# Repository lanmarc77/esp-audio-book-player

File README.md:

# TINAMP: An ESP32 based audio book player build from existing electronics modules
TINAMP: **T**his **I**s **N**ot **A** **M**usic **P**layer.  
  
This is a device that is meant to play non-DRM audio books from SD cards and has the following features:  

- folder based audio book player, one folder contains all files of one audio book
- multiple audio books supported (currently max. 9999 on one SD card with presorted index)
- sorting of audio book names and audio book files by ASCII name (see limitations of sorting below)
- saves audio book listening position and resumes for each audio book
- supports huge single file audio books, e.g. a 20hrs long singe file audio book
- file formats AMR-WB, MP3 and OGG
- ASCII character based menu driven UI for 16x4 character screen
- single rotary encoder navigation
- sleep timer 1...480min, wakeup timer 1min...24hr
- play speed settings from 0.5...2.5 in 0.05 steps (saved individually for each audio book)
- audio equalizer (saved individually for each audio book)
- endless auto repeat mode of selected audio book
- auto power off
- firmware upgrades from SD card
- based on pure esp-idf + esp-adf
- plays 50hrs+ with 2800mAh 18650 battery
- does not need nor use any wireless connection
- does not track the user in any way
- charging via USB-C
- endless options of integrations with speakers/cases
  
It tries to follow the design principle of
[doing one thing and doing that well](https://en.wikipedia.org/wiki/Unix_philosophy).
  
# The working prototypes
development board:

integrated in an old speaker that otherwise might have landed in the trash:  

the current portable/smaller prototype version (based on Hammond RL6215 case):  

first 3d print prototype with 80s vibes:  

[first POC (proof of concept)](pictures/first_poc.jpg)
  
# Why?
By the time of this writing (2023) one really needs to search hard to find an offline only non tracking audio book player that is
able to play files from huge SD cards and at the same time sorts the files based on their name and remembers and
resumes the last listening position.  
Many people nowadays will use subscription services with corresponding apps on their smartphone. These services
and the apps usually track the users build profiles suggest new audio books sell ads and more. Services like these can be canceled at any time. May it be for politics or economic reasons. They usually do not allow you to own the audio book but only sell a license to listen at it for as long as the company exists or is allowed to do business with you.  
I have an audio book collection that I created by only buying if I can download the files or copy them e.g. from a CD to keep them. Without any DRM.  
All my audio books are converted to and then stored in AMR-WB as for me the quality with 24kBit/s mono is good enough.
This shrinks an MP3 file to approx. 1/10ths when using AMR-WB and also makes the backup cheap. One CD with AMR-WB can hold 60hrs, a DVD 350hrs, a 25GB BD-R 2000hrs+.  
A 256GB SD card can hold around 2 years and 9 months of continuous listening in AMR-WB. Multiple SD cards can hold enough listening material for a life time.  
Using existing electronics hardware modules and the software of this repository I can now build a device that just plays my audio books. Not more, not less. And it most likely will do so in 30years assuming nothing breaks.
There are still 30yrs+ old Nintendo Gameboys that work like a charm and are being refurbished.  
Additionally I can change the behavior of the software as I like. The whole development environment works offline and can also be installed in an offline virtual machine and will still be able to compile even if the hardware manufacturer of the main controller board does not exist anymore.  
  
# Videos
Download and watch:  
[Scenario1](https://github.com/lanmarc77/esp-audio-book-player/raw/main/videos/scenario1.mp4): normal operation  
[Scenario2](https://github.com/lanmarc77/esp-audio-book-player/raw/main/videos/scenario2.mp4): seeking  
[Scenario3](https://github.com/lanmarc77/esp-audio-book-player/raw/main/videos/scenario3.mp4): sorting  
[Scenario4](https://github.com/lanmarc77/esp-audio-book-player/raw/main/videos/scenario4.mp4): auto bookmarks  
[Scenario5](https://github.com/lanmarc77/esp-audio-book-player/raw/main/videos/scenario5.mp4): sleep timer  
[Scenario6](https://github.com/lanmarc77/esp-audio-book-player/raw/main/videos/scenario6.mp4): wakeup timer  
[Scenario7](https://github.com/lanmarc77/esp-audio-book-player/raw/main/videos/scenario7.mp4): firmware upgrade  
[Scenario8](https://github.com/lanmarc77/esp-audio-book-player/raw/main/videos/scenario8.mp4): play speed, equalizer, repeat mode  
  
# Hardware
The build only needs a few components that are manufactured by companies in mass and therefore cheap.  
For PCB based components the schematics are available in the module datasheets folder.  
  
**Main controller board:**  
The main controller board is a Heltec WiFi Kit 32 V3. It was chosen because it has a very small deep sleep
current of about 10µA. I measured 15µA with nothing connected to it. Still very good. It already comes with
the circuitry to connect and charge a rechargeable battery as well as the possibility to disconnect other
components from power by using a software programmable power pin (Ve).  
Finally an OLED display is also already available for the UI.  
Be aware that you buy V3 of this board version as it has the low deep sleep current. Otherwise your battery
looses way too much energy even if you do not use the player. Additionally verify that you also get a fitting
battery cable.  
  
Typical price in Germany incl. tax (2023): 20€. 
  
**I²S digital analog audio converter**  
Currently only a MAX98357A based converter has been tested extensively. Also an UDA1334A and PCM5102 were
tested and they worked. Both of these stereo DACs needed around 10-15mA more current which will reduce the system
runtime.
The MAX98357A already contains an amplifier to directly connect it to a speaker and get a usable volume out
of it.  
  
Typical price in Germany incl. tax (2023): 8€. 
  
**SD card holder**  
I still had old big SD cards laying around so I started with a big SD card holder. They also exists in
micro sd card format. I used this model as it comes with the needed pullup resistors already on the PCB.
Additionally I removed the voltage regulator that is used to convert 5V to 3.3V as I drive the board already
with 3.3V and it consumed around 2mA if back fed. I tested SD cards up to 512GB with this board and they worked.  
  
Typical price in Germany incl. tax (2023): 1.5€. 
  
**Battery and holder**  
Any LiIon battery can be used. I tried 18650 and 14500 without any problems. I suggest trusted dealers as
there are many cheap fake batteries.  
  
Typical price in Germany for both incl. tax (2023): 8€. 
  
**Rotary encoder**  
To minimize wiring and drilling work I decided for a single rotary encoder as main navigation option. This model
has an integrated switch. I suggest to buy a version that comes with the washer/nut/cap.  
  
Typical price in Germany incl. tax (2023): 1€. 
  
**PCB**  
The prototypes as seen above use half or full size euro card PCBs. Any will do for manual wiring. You would
use the full size if you need the extra space for mounting it inside e.g. a speaker.  
  
Typical price in Germany incl. tax (2023): 2€. 
  
## Wiring diagram
Click on the picture for zoom.  

The original .odt file of this drawing is in the `src`directory.  
  
Pictures of manually wired PCB:  

These PCBs have headers for the components. You can leave these out but then need to make sure in 
which order you solder the wires as you might not get to them anymore.   
  
## Buyable manufactured PCB
WIP: One or two PCB layouts as motherboard for a 3D printed base case and a worldwide buyable case.  
First prototype PCB:  

## Printed/buyable case
WIP: 3D case model  
TODO: worldwide buyable model (most likely the Hammond RL6215)  
  
## Current measurements / battery life
The runtime of the system is highly dependent on the current consumption. The current consumption depends on the
type of audio played and mostly the volume. The following measurements were made using the
setup prototype development board as seen above with 8 Ohm speaker OWS-131845W50A-8, 3.7V, 4GB class 10 Transcend
microSD. An UNI-T UT61E with a 22µF tantal smoothing capacitor to handle the current peaks was used. Play speed
setting x1.0.  

| scenario                             | volume setting  | current |
|--------------------------------------|-----------:|------------:|
| switched off                         |  0%  | 19µA   |
| switched on, not playing, display on |  0%  | 37ma   |
| switched on, not playing, display off|  0%  | 34ma   |
| 128kbit/s mp3 44100 khz              | 50%  | 42ma   |
| 64kbit/s mp3 44100 khz               | 50%  | 42ma   |
| 128kbit/s mp3 22050 khz              | 50%  | 39ma   |
| 64kbit/s mp3 22050 khz               | 50%  | 39ma   |
| 128kbit/s ogg 44100 khz              | 50%  | 44ma   |
| 64kbit/s ogg 44100 khz               | 50%  | 44ma   |
| 128kbit/s ogg 22050 khz              | 50%  | 41ma   |
| 64kbit/s ogg 22050 khz               | 50%  | 41ma   |
| 24kbit/s amr 16000 khz               | 50%  | 41ma   |
| 128kbit/s mp3 44100 khz              | 75%  | 51ma   |
| 64kbit/s mp3 44100 khz               | 75%  | 51ma   |
| 128kbit/s mp3 22050 khz              | 75%  | 50ma   |
| 64kbit/s mp3 22050 khz               | 75%  | 50ma   |
| 128kbit/s ogg 44100 khz              | 75%  | 52ma   |
| 64kbit/s ogg 44100 khz               | 75%  | 52ma   |
| 128kbit/s ogg 22050 khz              | 75%  | 52ma   |
| 64kbit/s ogg 22050 khz               | 75%  | 52ma   |
| 24kbit/s amr 16000 khz               | 75%  | 52ma   |
| any file from before                 | 100% | ~105mA |
  
At high volumes the energy needed by the speaker dominates the current consumption. Also the current is not very stable and highly depends on the content that is actually played.  
The volume setting follows an x⁴ curve for translating % into power to fit our hearing.  
Depending on play speed settings the current consumption rises. This is due to the fact that more data needs to be handled and the CPU frequency is stepped up. Approximately 2mA per 0.1 step speed up.  
  
Real life tests resulted in a runtime of 54hrs:05mins playing 24kbit/s amr audio on QKZ AK6 earphones at 50% volume with a Murata / Sony Konion US18650VTC5D 2800mAh battery on firmware v00.00.08 (normal speed, no equalizer) from a 256GB Transcend SD card. A full charge after this test took 5hrs:15mins.  
  
# UI and player navigation
The following sub chapters explain the states of the player and the different menus or screens the player shows.  
You might want to watch the videos above for a short(er) introduction.  
  
The most common use case of an audio book player is powering it on, resume playing (maybe pause from time to time) and switching it off. This is currently done by pressing the rotary knob (for power on) which takes around 2s to right away jump into the last listened audio book and listening position, followed by another press of the rotary knob to start playing. Pressing the rotary knob while playing will pause the audio book player (and saves the listening position). Leaving it paused for 60s will power off automatically.  
  
## The rotary encoder
The only input device is a rotary encoder with a button. They are usually used as:  
  
- rotation for number, time and volume selections, speed of rotation in most menus increases the step size of the setup unit
- short click usually used for ok
- long click usually used as back, stop or cancel
- double click activates sub or special functions

## The players state machine
Legend:  
SC=short click  
LC=long click (or wait 10s in reduced functions mode)  
DC=double click  
AC=any type of click  
  
```
            powered off
                |
                | AC
                |                                              pressed long
                v       button still pressed?                    enough?   
            init screen ---------------------> reset countdown ---------- 
                |                                 screen                 |
                |                                    | button            |
                |                                    | released     reset screen
                |                                    |          +delete all bookmarks
                |                                    |            and user settings
                |                                    |                   |
                |                                    v                   |
                |<-------------------------------------------------------
                |
                | no sd card found?                      3s
                |--------------------> no sd card screen ---> power off
                |
                | new fw upgrade found?           SC                      10s
                |------------------> upgrade init ----> upgrade countdown --
                |                      screen              screen           |
                |                        |                  |               |
                |                        | any other        | AC         upgrade
                |                        | click            |            progress
                |                        | or no click      |            screen
                |                        v after 3s         v               |
                |<------------------------------------------                | ~10s
                |                                                           |
                |                                                           v
                |                                                         reboot
                |
                | ~2s
                v           0 folders?                               3s
          audio book scan -------------> no audio books found screen ---> power off
              screen
                | ~?s
                | scan time depends on number of audio books
                |
                v                    LC                                  3s
   ---> audio book selection screen ----> persist new fw ---> off screen ---> power off
  |     |     |       ^    ^      ^         if needed
  |     |     |SC     |    |      |
  |     |     |       |    |      |
  |     |     |       |    |      |
  |     |     |       |    |      |
  |     |     |       |     ----   -
  |     |     |       | AC      |   |
  |     |     v       |         |   |<-------------------------
  |     |    audio book content |   |                          |
  |     |    |   scan screen    |   |                          |
  |     |    |    |             |   |       next sub screen    |
  |     |    |    | 0 files     |   |       ---------------    |
  |     |    |    | found?      |   |      |               |   |
  |     |    |    |             |   |      v            SC |   |
  |     |    |     -------------    |    play overlay ----     |
  |     |    |                      |    screen                |
  |     |    | scan      -----------     |3s  ^                |
  |     |    | finished |                |    | rotate         |
  |     |    |          | LC             |    |                | LC
  |     |    v          |       SC       v    |       SC       |
  |     |    pause screen  <----------> playing <-----------> pause screen
  |     |    with chapter  <----------  screen <------         with time
  |     |     selection            LC     |           |        selection
  |     |                                 | DC        |
  |     |                                 |        play next
  |     |                                  -------> chapter
  |     |
  |     |
  |     | select audio book "0"
  |     |  named setup screen
  |      -----------------
  |                       |          next settings
  |      LC               v             screen
   ---------------- global settings <--------------
                      ^   |     |           rotate |
                      |   | SC   ------------------
      ----------------    |
     |                    |
     |                    v                change value
     |           any chosen setup screen <--------------
     |           |              |  |            rotate  |
     |           | SC           |   --------------------
     |           | means ok     |
     |           |              | any other
     |           | for wakeup   | click cancels
     |           | timer:       | for wakeup timer:
     |           | activated    | deactivated
     |           v              |
      --------------------------

```

After 30s of no click the screen turns off. If the player is not playing and the screen was off for an additional
30s then the player powers off.  
If the screen is off any click will first turn the screen on. An additional click is needed for the desired action. There is one exception: the double click in the play screen to skip to the next chapter works right away even if the screen is off.  
If the battery level drops below 3.35V the low battery screen is shown and the player powers off.  
  
## The menus
All menus are built upon the basic ASCII set. This should allow changing the display easily.  
If something can be setup using rotation usually that element flashes.  
  
### Init screen
```
 ----------------
|                |
|     (o_o)      |
|       ok       |
|   v00.00.08    |
 ----------------
```
Shows the firmware version number. If ok is displayed the firmware is persisted. If TEST is displayed
the firmware is not persisted and if the player powers off automatically the old firmware is reinstalled.  
  
### Reset countdown screen
```
 ----------------
|                |
|     (o o)      |
|       O        |
|[=========-    ]|
 ----------------
```
If the button is hold down until the progress bar at the bottom has counted down the player
will delete all bookmarks and reset all user settings to default values.  
  
### Reset screen
```
 ----------------
|0000000000000000|
|0000000000000000|
|0000000000000000|
|0000000000000000|
 ----------------
```
Shown until the reset procedure is finished.  
  
### Upgrade init screen
```
 ----------------
| ||    00.00.07 |
|-  -     vvv    |
|-  -      ?     |
| ||    00.00.08 |
 ----------------
```
Shows the currently installed firmware and the new version that can be installed.  
  
### Upgrade countdown screen
```
 ----------------
| ||    00.00.07 |
|-  -     vvv    |
|-  -     5s     |
| ||    00.00.08 |
 ----------------
```
A countdown counts down to signal the upgrade will be started.  
  
### Upgrade screen
```
 ----------------
|       ||       |
|    -  34% -    |
|    -      -    |
|       ||       |
 ----------------
```
Progress is shown during the running upgrade procedure.  
  
### No SD card screen
```
 ----------------
|    -------     |
|   | SD ?  |    |
|   |______/     |
|                |
 ----------------
```
This screen is also shown if the SD card is removed while the player is active.  
  
### Audio book scan screen
```
 ----------------
|     |---|      |
|     | ? |      |
|     |---|      |
|[===    .      ]|
 ----------------
```
The progress bar at the bottom shows the progress of the scan an sorting process.  
  
### No audio books found screen
```
 ----------------
|     |---|      |
|     | 0 |      |
|     |---|      |
|                |
 ----------------
```
### Audio book selection screen
```
 ----------------
|audio book name |
| |------------| |
| |     12/121 | |
| |*---00:01---| |
 ----------------
```
Using rotation the different audio books can be selected. The screen shows selected 12 of 121 audio books.
The audio book name at the top is the name of the folder and scrolls through the screen if it is long.  
The value 00:01 is only shown if the wake up timer has been setup and activated and shows the setup value.  
If an ```!``` is shown it means a bookmark exists for this book. If an ```*``` is shown the bookmark is at a position >95% of the last track of this book.  
  
### Audio book content scan screen
```
 ----------------
| |------------| |
| |  A <==> B  | |
| |------------| |
|[=====- .      ]|
 ----------------
```
The progress bar at the bottom shows the progress of the scan and sorting process and A and B are animated.  
The sorting can be canceled if it takes too long by using any click.  
  
### Pause screen
```
 ----------------
|audio book name |
|      3/12 3m  8|
|     12:22 |>  9|
|[===-   .      ]|
 ----------------
```
The audio book name at the top is essentially the name of the folder and scrolls through the screen if it is long.  
3/12 shows the currently selected chapter (=file) of this audio book and the number of all chapters.  
12:22 is the current time within the currently selected chapter.  
Depending on the mode either the time or the chapter flashes meaning this can be changed (seek or skip) using rotation.  
The value 3m is only displayed if a sleep timer was setup and activated and shows the time left until the player will power off.  
The progress bar at the bottom shows the progress within the current chapter.  
On right side the battery level in percent is shown.  
    
### Playing screen
```
 ----------------
|audio book name |
|      3/12 3m  8|
|     12:22 ||  9|
|[===-   .      ]|
 ----------------
```
The audio book name at the top is essentially the name of the folder and scrolls through the screen if it is long.  
3/12 shows the currently selected chapter (=file) of this audio book and the number of all chapters.  
12:22 is the current time within the currently selected chapter.  
The time is switching repeatedly between current time position and time left.  
The value 3m is only displayed if a sleep timer was setup and activated and shows the time left until the player will power off.  
The progress bar at the bottom shows the progress within the current chapter.  
On right side the battery level in percent is shown.  
If an asterisk ```*```  is shown beside the pause symbol ```||``` then repeat mode for this audio book is active.  
Sometimes a countdown is shown in the middle of the progress bar. It counts the amount of seconds left until the play overlay screen sub menu position is switching back to volume.  
  
#### Play overlay screen
```
     volume               sleep timer
 ----------------      ----------------  
|################|    |                |
|################| -> |    (-_-)Zzz    |
|##              |    |      1/99m     |
|      5100      |    |                |
 ----------------      ----------------
        ^                     |
        |                     v
        |                 play speed
        |              ----------------  
        |             |                |
        |             |     >>>>>>>>   |
        |             |      x1.20     |
        |             |                |
        |              ----------------
        |                     |
        |                     v
  repeat mode              equalizer
 ----------------      ----------------  
|                |    |                |
|  |>  -->  ||   | <- |     normal     |
|                |    |                |
|                |    |                |
 ----------------      ----------------
```
The play overlay screen is activated when a file is played and the rotary encoder is turned. If it is active a short click is going through the different settings. This screen will automatically switch back to the play screen after 3s of no user input but will remember for 8 more seconds at which sub menu it was left.  
  
Volume: The # characters are a visual representation of the setup volume. Volume level ranges from 0...10000. 7500 actually marks 100% audio volume of the source everything above this will add a gain of up to 25% to the source volume level.  
  
Sleep timer: Using rotation the sleep timer can be setup from 1 minute to 99 minutes in minute precision. Time automatically starts if a value is setup and is canceled if - is displayed.  
  
Play speed: Using rotation the speed can be setup. Play speed is changed instantly and stored individually for each audio book.  
  
Equalizer:  Using rotate you can choose between the different equalizer presets. The setting is stored individually for each audio book.  
  
Repeat mode:  Using rotate one can choose to enable folder repeat (<-->) or not (-->). The setting is stored individually for each audio book.  
  
### Low battery screen
```
 ----------------
|      _--_      |
|     |    |     |
|     |    |    6|
|     |####|     |
 ----------------
```
On the right side the battery level in percent is shown.  
  
### Off screen
```
 ----------------
|                |
|    (-_-)Zzz    |
|    241160MB    |
|     15/2%      |
 ----------------
```
Also shows the size of the detected SD card, the number of stored bookmarks and the used space of the bookmark storage in the SPIFFS of the ESP32.  
  
### Global settings/functionality
The setup is entered by scrolling to audio book "0". The following screen is displayed:  
```
 ---------------- 
|     *******    |
|   /  Setup  \  |
|   \         /  |
|     *******    |
 ----------------
```
Setup is entered with a single click and left with a long click.  
It has the following internal layout:  
```
   wakeup timer         screen rotation
 ----------------      ----------------
|       1/8      |    |       2/8      |
|(-_-)  ->  (o_o)| -> |   -------->    |
|                |    |  |    0    |   |
|      01:00     |    |   <--------    |
 ----------------      ----------------
        ^                     |
        |                     v
     firmware           screen brightness
     persist               settings
 ----------------      ----------------
|       8/8      |    |       3/8      |
|     persist    |    |\\\\\\    //////|
|     firmware   |    |       100      |
|        ?       |    |//////    \\\\\\|
 ----------------      ----------------
        ^                     |
        |                     v
     reduced           rotary encoder
      mode                direction
 ----------------      ----------------
|       7/8      |    |       4/8      |
|       all      |    | o o            |
|    functions   |    |o   o    -->+   |
|                |    | o o            |
 ----------------      ----------------
        ^                     |
        |                     v
     bookmark           rotary encoder
     deletion               speed
 ----------------      ----------------
|       6/8      |    |       5/8      |
|   Bookmarks    | <- | o o            |
|    10 -> 0     |    |o   o     x1    |
|       ?        |    | o o            |
 ----------------      ----------------
```
After entering the global settings the rotary knob can be used to select the setting to change.  
A short click will enter the specific setting selected.  
On top a counter for all settings is shown.  
If this menu is left with a long click all settings that are saveable are saved.  
  
#### Wake up timer setup screen
```
 ----------------
|                |
|(-_-)  ->  (o_o)|
|                |
|      01:00     |
 ----------------
```
Using rotation the wakeup timer can be setup from 1 minute to to 24 hours in minute precision.  
This setting is not stored. It always starts with 1 hour after the player started.  
Once the timer was activated its setup time starts counting **after** the player was shutdown independent if the shutdown was initiated manually or by a sleep timer.  
  
#### Screen rotation setup
```
 ----------------
|                |
|   -------->    |
|  |    0    |   |
|   <--------    |
 ----------------
```
This allows rotating the screen by 180°. 0 stands for default and 180 for 180° rotated setting.  
This setting is stored and reloaded on each player start.  
  
#### Screen brightness setup
```
 ----------------
|                |
|\\\\\\    //////|
|       100      |
|//////    \\\\\\|
 ----------------
```
This allows to setup the brightness of the screen. Step size is +/-5 and ranges from 0 to 250.  
This setting is stored and reloaded on each player start.  
  
#### Rotary encoder direction setup
```
 ----------------
|                |
| o o            |
|o   o    -->+   |
| o o            |
 ----------------
```
This allows switching the turn direction of the rotary knob. Left turns are getting right turns and vice versa.  
This setting is stored and reloaded on each player start.  
  
#### Rotary encoder speed setup
```
 ----------------
|                |
| o o            |
|o   o     x1    |
| o o            |
 ----------------
```
This allows changing the speed of the rotary knob. One can choose that every dent of the rotary encoder is used (x1) or only every 2nd dent (x0.5).  
This setting is stored and reloaded on each player start.  
  
#### Bookmark deletion
```
 ----------------
|                |
|   Bookmarks    |
|    10 -> 0     |
|       ?        |
 ----------------
```
Shows the number of bookmarks that can be deleted using a short click without deleting other settings.  
  
#### Reduced functions mode
```
 ---------------- 
|                |
|       all      |
|    functions   |
|                |
 ----------------
```
If reduced functions only the normal single click is an accepted rotary knob action. The long press (usually back) of the rotary knob is disabled and instead substituted by a 10s time delay. If 10s nothing is pressed the menu is automatically left.  
Additionally the overlay only allows setting up volume with no further sub menus like play speed. Also no double click is accepted.  
This mode is meant for elderly persons who might have difficulties with all the possibility and just want to select and audio book and listen to it.  
  
#### Firmware accept
```
 ---------------- 
|                |
|     persist    |
|     firmware   |
|        ?       |
 ----------------
```
If the firmware was just upgraded the firmware can be kept with this menu point. If the firmware was persisted already it shows OK instead of a question mark.  
If the firmware is not persisted after an upgrade and the player is shutdown the player will rollback the firmware to the previous one.  
  
# Uploading initial binary release
For a brand new main controller board an initial upload is needed. This initial upload will setup the correct partition details and installs the firmware for the first time. After this initial upload firmware upgrades via the SD card are possible.  
The binary release files in the [release](https://github.com/lanmarc77/esp-audio-book-player/releases) section:  
  
- bootloader.bin
- partition-table.bin
- ota_data_initial.bin
- esp32_player.bin
  
are to be used for this initial upload.  

## Linux and Windows
For Linux and Windows the Espressif esptool.py can be used. It can be installed by following [this guide](https://docs.espressif.com/projects/esptool/en/latest/esp32/).  
A Windows Comport driver can be found in the `src` directory.  
  
The command line for the initial upload should look like this:  
`
esptool.py -p [YOUR PORT e.g. COM7 or /dev/ttyUSB0] -b 460800 --before default_reset --after hard_reset --chip esp32s3 write_flash --flash_mode dio --flash_freq 80m --flash_size 4MB 0x0 bootloader.bin 0x10000 esp32_player.bin 0x8000 partition-table.bin 0xd000 ota_data_initial.bin
`  
  
Since v00.00.03 firmware upgrades are possible via SD card if this initial upload was done.  
  
## Windows using the Flash Download Tools
Espressif also offers the Windows only Flash Download Tools package with a graphical user interface.  
It can be downloaded from [here](https://www.espressif.com/en/support/download/other-tools).  
A Windows Comport driver can be found in the `src` directory.  
  
The following settings need to be made for the initial upload:  
  
Select the correct COM port after making the settings as seen below and press START:  
  
Ideally no errors are shown and the initial upload is finished.  
  
# FW upgrade using SD card (incl. rollback support)
For upgrading firmware once the initial upload was done only one specific file from the
[release section](https://github.com/lanmarc77/esp-audio-book-player/releases) is needed: XX.XX.XX_ota.fw  
XX are letters from A-F or/and numbers from 0-9 specifying the firmware version of this release.  
Place the file on the SD card in a folder called `fwupgrade`. Once you start the device it should present you with the upgrade screen. The upgrade screen is left without upgrading if no user interaction is happening for 10s.  
If you wish to upgrade shortly press the encoder button. A countdown of 10s gives you the possibility to stop the upgrade if you press the encoder button. Once the upgrade started you can not interrupt it.
The actual writing process for the upgrade takes around 10s and the progress is shown.  
  
If everything worked you should now see the device restart with the new firmware version but it displays
"TEST" instead of "ok" in the initial firmware version screen during startup.  
"TEST" means that the new firmware is not yet persisted. In this test state you have the possibility
to test everything and check if the new version suits your needs.  
You can persist the new firmware by manually switching the device off by long pressing the encoder button
in the audio book selection screen.  
If you do not want to keep the new version and rollback you need to wait for the
device to auto power off which usually happens after 1 minute with no user interaction. Once auto powered off and
afterwards started again the old version should be activated again.  
  
# Compilation hints
Currently used espressif sdk versions:  
esp-idf:  v5.3.2/commit 9d7f2d69f50d1288526d4f1027108e314e8c879f  
esp-adf:  v2.7/commit 9cf556de500019bb79f3bb84c821fda37668c052  
  
Needed for exFAT:   
To enable exFAT file esp-idf/components/fatfs/src/ffconf.h needs to be adjusted.  
  
Optionally for more privacy:  
The esp-adf unnecessarily links components which on every compilation results in checks with the servers for updates by the component manager.  
To be able to compile completely offline adjustments to the sdk source trees were made.
  
Take a look into the `src/patches/` directory for the .patch files to apply to above sdk versions.
  
# Software architecture
  
```

 -----------------
|   ssd1306*.*    |           -----------------------
|                 |          |       battery.*       |
| low level I²C   |          |                       |
| functions for   |          | monitors, filters     |
| OLED and fonts  |          | and offers the        |
|                 |          | current battery level |
 -----------------           |                       |
         ^                   | uses task             |
         |                   |                       |
         | calls              -----------------------
         |                     ^
 --------------------          |
|   ui_elements.*    |         | calls
|                    |         |
| offers reusable    |         |
| UI elements        |         |                                   --------------------------
|                    |         |    ---------------------------   |         sd_play.*        |
 --------------------          |   |     rotary_encoder.*      |  |                          |
           ^                   |   |                           |  | plays files from SD card |
           |                   |   | low level rotary encoder  |  | using esp-adf pipelines  |
           | calls             |   | and switch handling       |  |                          |
           |                   |   |                           |  |                          |
 ------------------------      |   | uses task + interrupt     |  | uses tasks               |
|       screens.*        |     |   |                           |  |                          |
|                        |     |    ---------------------------    --------------------------
| creates and displays   |     |     ^                              ^                      |
| complete screen        |     |     |                              |                      |
| layouts                |     |     | calls                        | calls                |
|                        |<-   |     | queue communication          | queue communication  |
 ------------------------   |  |     |                              |                      |
                            |  |     |           -------------------                   ----
                      calls |  |     |          |                                     |
                            |  |     v          v                               calls |
 -----------             --------------------------                                   v
|   main.*  |           |        ui_main.*         |             --------------------------
|           |  calls    |                          |            |      format_helper.*     |
|  basic    | --------> |    main player logic     |    calls   |                          |
|  board    |           |                          | ---------> | functions to get audio   |
|  init and |           |   state machine based    |            | format specific          |
|  deinit   |           |                          |            | information like         |
|           |           |                          |            | runtime and bitrate      |
 -----------            |                          |            |                          |
                        |                          |             --------------------------
       ---------------- |                          |
      |                 |                          |<-----------
      |                  --------------------------             |
      |                                |                        |
      | calls                          | calls                  | calls +
      |                                |                        | queue communication
      v                                v                        v
 --------------------         ----------------------         -----------------------------
|     sd_card.*      |       |        saves.*       |       |        ff_handling.*        |
|                    |       |                      |       |                             |
|  low level SPI     |       | handles save         |       | reads and sorts dirs/files  |
|  bus handling and  |       | restore and house    |       | an returns sorted lists     |
|  VFS mount/umount  |       | keeping of bookmarks |       |                             |
|                    |       | and player settings  |       | uses task for sorting       |
 --------------------        |                      |       |                             |
                              ----------------------         ------------------------------

```  
The following sub chapters will give an insight into each shown component and its architecture ideas.  
This layout shows the ideal model that only very rarely is broken in the code.  
  
## main.*
The entry point of the application. It initializes the board and sets up the CPU, disables WiFi and
hands over to the other components.  
Function main() is never left but if other components finish powers off the board and sets up a
wake up timer if needed.  
  
## ui_main.*
This component implements the main player logic. A state machine represents the navigation of the user
and the state the player is currently in.  
As the central component it makes direct use of a all the other components.  
  
## sd_card.*
This component initializes the SPI bus for usage with an SD card and tries to mount the SD card
into the ESPs VFS so it can be used by all other components using file access functions.  
  
## rotary_encoder.*
This component initializes and monitors the rotary encoder and switch using a task and and interrupt.  
Events are generated and placed as messages into a queue for communicating with other components.  
  
## battery.*
This component initializes and monitors the AD converter for monitoring the battery level.  
There are two battery levels available. With slower noise filtering and with faster more noisy filtering.  
A task samples the battery voltage every 500ms.  
  
## screens.\*, ui_elements.\*, ssd1306\*.\*
This collection of components uses a typical layered approach.  
The ssd1306 functions give access to a physical display. Here the OLED of the board.  
The ui_elements functions use the ssd306 functions to offer reusable UI elements like text output or
progress meters with which larger screen layouts can be built.  
The screens functions use the ui_elements functions to create a complete screen layout for the player.  
It is assumed that the display can handle a layout of 16x4 ASCII characters.  
  
## saves.*
This component handles the storage, retrieval and house keeping of bookmarks and the settings (like volume)
if the player. It makes use of the ESP VFS system and currently stores everything in the internal SPIFFS.  
It also takes care of initializing the SPIFFS.  
  
## ff_handling.*
This component scans folders and files within folders and delivers a sorted list. It uses a task for the
longer running scanning and sorting process and communicates its progress via a queue. The scanning and
sorting process can also be canceled via queue communication. During scanning and sorting the CPU
frequency is increased to speed up the process.  
  
## format_helper.*
This component offers audio file format functions. One can convert byte position <-> time stamp and
determine sample rates and bitrates and further information to setup the esp-adf pipeline correctly
right from the start.  
  
## sd_play.*
This components tries to abstract all the esp-adf functionality of playing an audio stream with in the pipeline.
It combines SD card access by allowing to start playing a file from the SD card using a task.  
Using queues the components can be instructed to start/stop the playing and contentiously reports the current
playing position for the user interface.  
The resume function that actually is not out of the box supported by a pipeline based streaming approach is
implemented by adding an own file stream handler within the pipeline that takes care of at first delivering needed
header information for the decoder but then jumps within the file to the position to resume from.  
  
## naming conventions
Filenames and global variables/functions match each others prefixes to easily be able to locate them.  
Prefixes are written in capital case and use _ as separator.  
Apart from the prefixes variables and functions use camel case.  
  
# Limitations, design decisions and behavior descriptions
The following sub chapters explain a few design decisions, limitations and system behavior.  
  
## Sorting, limits of files/folders
Sorting on a µC is hard. Sorting algorithms trade speed with memory and memory is something a µC usually does not have
very much. It is impossible to keep a huge root directory in memory depending on the the character length of each
entry. Especially if you want to be deterministic on how many entries you support.  
This projects implementation has two options of displaying and playing sorted entries.  
  
### Sorting each time
This is the default implementation. After startup when the list of all available audio books is read this list is sorted.
Instead of keeping the strings/names of all entries in memory only their file allocation table position is used. This position acts as kind of ID of the entry. This ID is then sorted inside an array but not by its value but by its corresponding name.
This means that the algorithm always has to translate between ID and name of the file resulting in an increased
time of sorting. The algorithm used is a selection sort with a complexity of O(n²). But it is memory deterministic.  
This allows keeping 1000 entries with only 2kB of memory usage. To always wait for 1000 entries to be sorted is also still acceptable.  
Sorting speed is also determined by the way entries are named. As the C function strcmp is starting to compare at the beginning of a string the earlier a mismatch happens the earlier it can stop. It is beneficial to name files e.g. 01... , 02... instead of ...01, ...02.  
If a directory contains more than 1000 entries they are not taken into account.  
This described sorting applies for audio books (directories) and their content (files).  
  
### Presorted list of root directory
As I wanted the player to be able to also hold large collections of audio books 1000 entries in the root directory did not seem enough.  
But sorting would take too long to be acceptable. Instead a presorted entry list can be created. Much like an .m3u file.  
The file needs be called `presorted.txt` and must reside in the root directory of the SD card. It can contain 9999 lines where each line contains the directory name. The order in the file is the order in which they are displayed in the player.  
The following command chain can be used in the root directory of the SD card to create such a sorted file:  
  
`find * -type d -print | sort | iconv -t 437 > presorted.txt`  
  
Names of entries are expected to be in code page 437 format as this is the only one that is enabled in the ESP32. I did not wanted to make things more complicated by supporting all kinds of character encodings.  
9999 entries=audio books with an average length of an audio book of 6hrs would take almost 55 years of listening if you listen every single day for 3hrs.  
  
For this 9999 entries limit to kick in:  

-  for AMR-WB file format with 24kbit/s an SD card would need to have ~618GB  
-  for MP3 file format with 128kbit/s an SD card would need to have ~3.3TB  

This implementation limit should not be relevant much while using the player.  
  
As the number of files within a directory/audio book are usually below 1000 the presorted.txt is not implemented for these.
  
## Bookmarks
I decided to implement the bookmark storage inside the SPIFFS of the ESP32. I reserved 512kB for the SPIFFS. The
storage could also have been the SD card and would have been the first choice. But that would mean writing to the
SD card. The same card where the audio books are stored. I did not wanted to risk file system problems if one of those
writes failed. Meaning a destroyed file system not being able to listen to audio books anymore. This project never
writes to the SD card which in turn never can get corrupted.  
Each bookmark is written when the player is paused or is powered off by one of the automatic methods like low battery
or sleep timer. A bookmark is a file in the SPIFFS. The name of the file is an MD5 hash constructed from the directory
name of the audio book. Inside the bookmark the listening position is stored and the file name that was currently played.  
  
Depending on the length of the file name bookmarks take more or less space in SPIFFS. On average 1kb can be assumed. This means around 500 bookmarks can be stored. Deleting individual bookmarks is not possible. To delete all bookmarks one can use the overall reset procedure or starting with firmware v00.00.08 the global settings menu, sub menu delete bookmarks.  
The powering off screen displays the usage of the SPIFFS in percent and the number of bookmarks.  
There is also an automatic bookmark deletion procedure implemented. If the SPIFFS usage level is above 75% the currently used SD card and the bookmarks are scanned and compared. If there are bookmarks in the SPIFFS for which no fitting directory on the SD card exists this bookmark is deleted. This house keeping idea is based on the use case that SD cards are being rewritten over and over with new audio books where the old ones are deleted. Ideally for this use case one should never be needed to manually delete old bookmarks.  
  
Manual bookmarks are not supported. Mainly because I personally never needed them but also because house keeping gets
much more complicated as well as a method of jumping to different bookmarks inside the same audio book must be implemented.  
  
## CBR/VBR
Only fully supported are CBR encoded files. The player also plays VBR files but the displayed timestamps might be wrong.
Without scanning the full file or implementing code for the various VBR indexes there is no way to determine a correlation of file position and time.  
The format handler functions take a look at the first frame of a file to determine the bitrate and therefore the frame length of a file. This data is then assumed to be valid for the whole file.  
  
## Metadata
No metadata of files is used. This includes chapter indexes, subtitles or cover pictures.  
  
## Bluetooth audio
The used µC board uses the ESP32-S3. This newer model of the ESP32 does not support the so called classic Bluetooth
audio stack which uses SBC as codec. It only supports the not yet widely used Bluetooth Audio LE. The esp-adf does
not yet support a pipeline element that uses Bluetooth Audio LE. Once support is added in the esp-adf pipeline system and devices are getting more common I might implement support for it.  
It might also be possible to make this project compile with the classic ESP32 that does support classic Bluetooth using SBC.
But I do not plan for this as I use headphones with a jack and no extra battery I need to take care of.  
  
## Audio processing
The ESP32 starts with the lowest possible CPU speed of 80Mhz. This is not enough CPU power if certain audio processing
options are enabled. Especially if the play speed has a high setting 80Mhz is not enough for the calculations needed. 
The program increases CPU speed to 160Mhz when play speed is getting greater than 1 and to 240Mhz for value greater 2.
This will increase power consumption and reduce system runtime.  
  
# Ideas/future
- multi user support with individual bookmarks
- audio navigation for handicapped people
- refactoring of code especially the huge ui_main.c

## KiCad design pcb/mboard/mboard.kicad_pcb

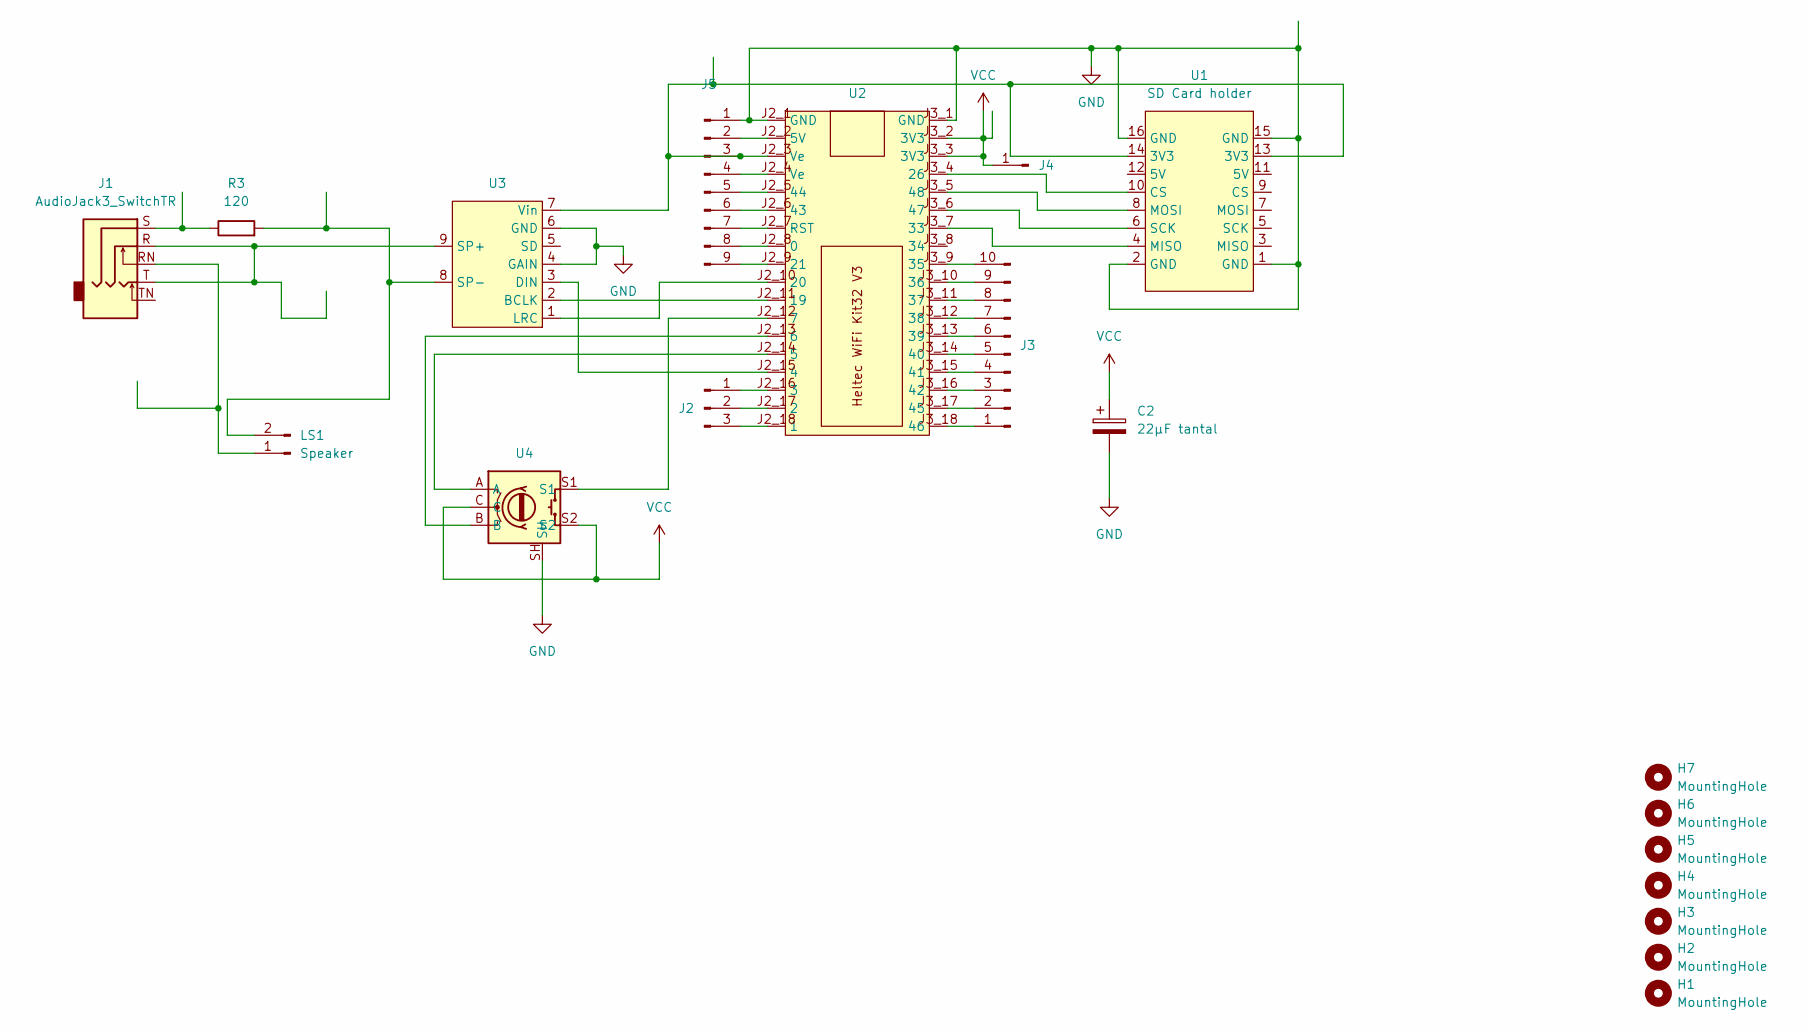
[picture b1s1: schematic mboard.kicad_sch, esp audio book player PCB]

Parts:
C2: 22µF tantal; CP_Radial_D5.0mm_P2.50mm
H1, H2, H3, H4, H5, H6, H7: MountingHole; MountingHole_2.7mm
J1: AudioJack3_SwitchTR; Jack_3.5mm_CUI_SJ2-3593D-SMT_Horizontal
J2: Conn_01x03_Pin; PinHeader_1x03_P2.54mm_Vertical
J3: Conn_01x10_Pin; PinHeader_1x10_P2.54mm_Vertical
J4: Conn_01x01_Pin; PinHeader_1x01_P2.54mm_Vertical
J5: Conn_01x09_Pin; PinHeader_1x09_P2.54mm_Vertical
LS1: Speaker; PinHeader_1x02_P2.54mm_Vertical
R3: 120; R_Axial_DIN0309_L9.0mm_D3.2mm_P15.24mm_Horizontal
U1: SD Card holder; SD_CARD_HOLDER_1
U2: Heltec WiFi Kit32 V3
U3: MAX98357A_BREAKOUT
U4: PEC16

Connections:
GND: C2.2, J5.1, U1.1 (GND), U1.2 (GND), U1.15 (GND), U1.16 (GND), U2.J2_1 (GND), U2.J3_1 (GND), U3.4 (GAIN), U3.6 (GND), U4.SH
unnamed: J1.S, R3.1
unnamed: J2.1, U2.J2_16 (3)
unnamed: J2.2, U2.J2_17 (2)
unnamed: J2.3, U2.J2_18 (1)
unnamed: J3.1, U2.J3_18 (46)
unnamed: J3.2, U2.J3_17 (45)
unnamed: J3.3, U2.J3_16 (42)
unnamed: J3.4, U2.J3_15 (41)
unnamed: J3.5, U2.J3_14 (40)
unnamed: J3.6, U2.J3_13 (39)
unnamed: J3.7, U2.J3_12 (38)
unnamed: J3.8, U2.J3_11 (37)
unnamed: J3.9, U2.J3_10 (36)
unnamed: J3.10, U2.J3_9 (35)
unnamed: J5.2, U2.J2_2 (5V)
unnamed: J5.3, U1.13 (3V3), U1.14 (3V3), U2.J2_3 (Ve), U3.7 (Vin)
unnamed: J5.4, U2.J2_4 (Ve)
unnamed: J5.5, U2.J2_5 (44)
unnamed: J5.6, U2.J2_6 (43)
unnamed: J5.7, U2.J2_7 (RST)
unnamed: J5.8, U2.J2_8 (0)
unnamed: J5.9, U2.J2_9 (21)
unnamed: J1.RN, LS1.1
unnamed: LS1.2, R3.2, U3.8 (SP-)
unnamed: U2.J2_15 (4), U3.3 (DIN)
unnamed: U2.J2_14 (5), U4.A
unnamed: U2.J2_13 (6), U4.B
unnamed: U2.J2_12 (7), U4.S1
unnamed: U2.J2_11 (19), U3.2 (BCLK)
unnamed: U2.J2_10 (20), U3.1 (LRC)
unnamed: U1.10 (CS), U2.J3_4 (26)
unnamed: U1.4 (MISO), U2.J3_7 (33)
unnamed: U1.6 (SCK), U2.J3_6 (47)
unnamed: U1.8 (MOSI), U2.J3_5 (48)
unnamed: J1.R, J1.T, U3.9 (SP+)
VCC: C2.1, J4.1, U2.J3_2 (3V3), U2.J3_3 (3V3), U4.C, U4.S2

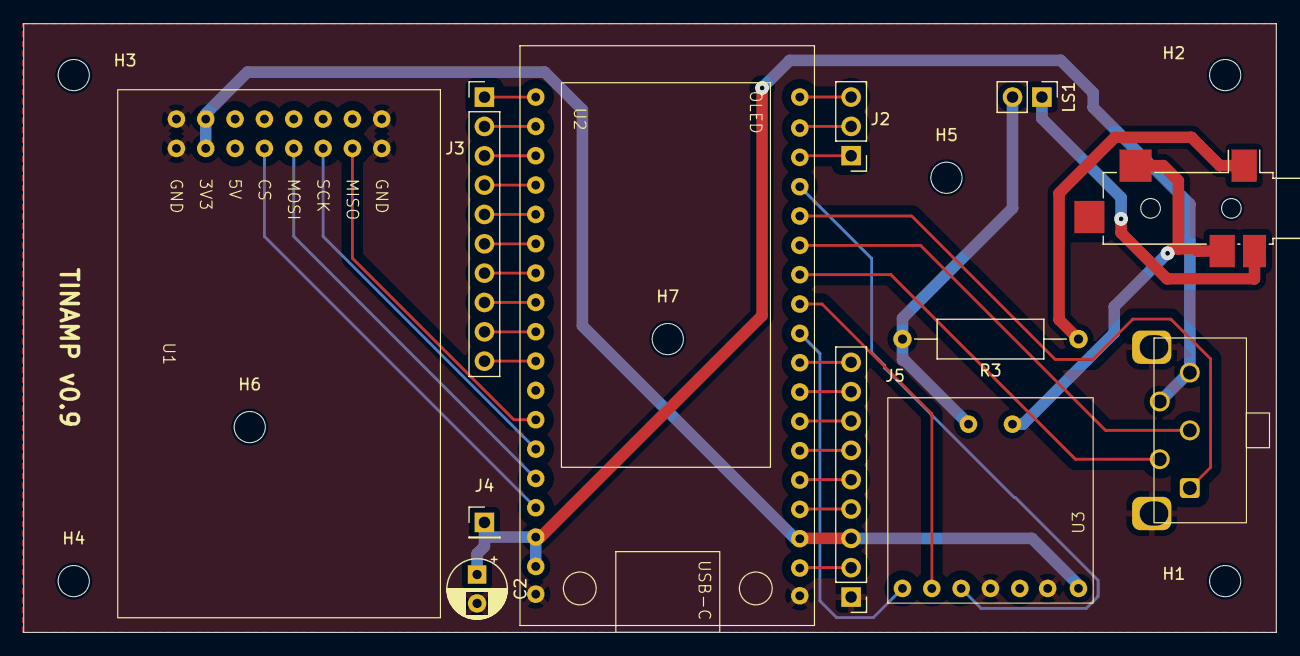
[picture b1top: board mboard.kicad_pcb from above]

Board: 2 copper layers, 108.5 x 52.7 mm, 19 parts (0 on the bottom side), 37 nets.

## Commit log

2023-12-17 added video links
2023-12-17 added sources
2023-12-18 added firmware upload details
2023-12-18 fixed typo
2023-12-19 added mobile version picture
2023-12-21 added current measurements and PCB pictures
2023-12-30 added volume fadeout for sleep timer, added wake up timer using RTC, faster sorting by increasing CPU speed shortly, documentation of public .h files, videos for firmware upgrade and wake up timer us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
2023-12-30 more documentation
2024-01-11 resetting of i2s only if not yet setup correctly to avoid DACs pops volume=7500 now means 100% source volume, volume=10000 now means 125% source volume optimized pipeline VolumeFilter buffer size for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
2024-01-11 add missing file
2024-01-12 added a LOT of documentation
2024-01-14 added equalizer and play speed settings
2024-01-19 added play speed settings, equalizer and repeat mode
2024-04-14 added global settings menu added new settings: screen rotation, rotary encoder speed and direction more documentation
2024-04-28 - moved sleep timer to play overlay menu - show countdown for play overlay sub menu reset - allow deletion of bookmarks via global settings - display number of bookmarks in shutdown screen
2024-07-14 - added brightness settings - first POC of 3d case model (good for testing but definitely not the final one)
2024-11-26 fixed uint32_t overflow bug with sleep timer >72min default to seek time mode for one chapter audio books
2024-12-08 - fixed bug introduced with 00.00.0A when entering an audio book for the first time with 1 book initially is not seekable - fixed AMR bitrate detection - fixed bug displaying wrong play position info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
2025-01-02 SDK Updates, new features, bugfixes - updated espressif sdk versions to idf v5.3.2, adf v2.7 - fixed mpeg version 2 layer 3 format handling - now showing bookmark hint in book selection screen - redu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
2025-05-25 - added a reduced functions mode - changed the way the global setup is entered - moved fw accept to settings screen
